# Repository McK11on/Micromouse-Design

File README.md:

# MicroMouse
Design and implementation of a micromouse robot for competitions, implementing filling algorithm and other technologies

| Layout | PCB_1 | PCB_2 |
|--------|-------|-------|
|  |  |  |

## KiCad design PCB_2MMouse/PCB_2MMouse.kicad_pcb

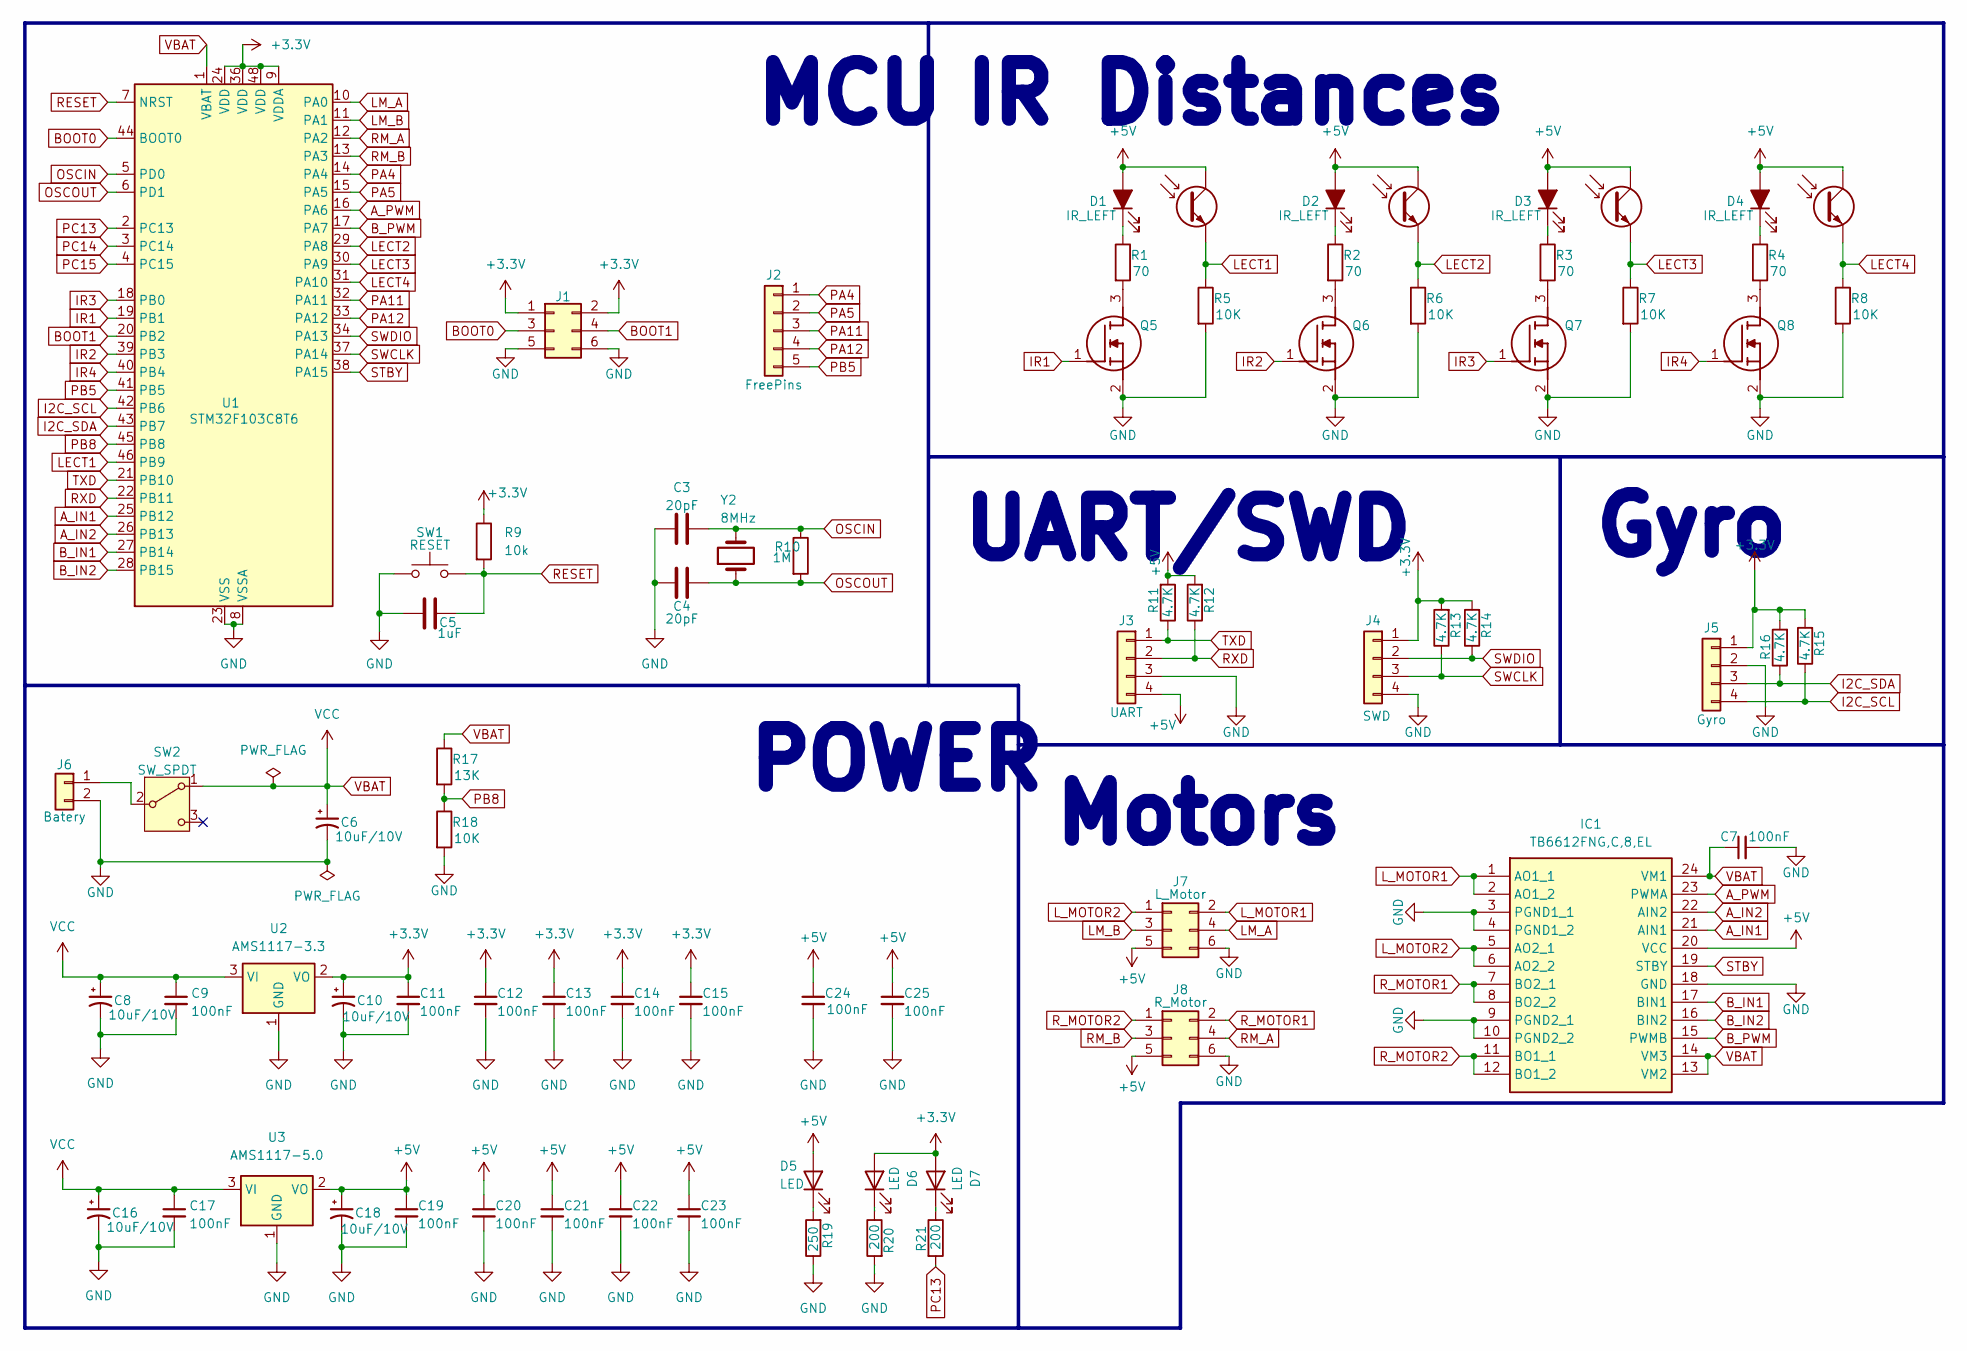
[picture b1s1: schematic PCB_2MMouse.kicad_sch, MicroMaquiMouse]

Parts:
C3, C4: 20pF; C_0805_2012Metric
C5: 1uF; C_0805_2012Metric_Pad1.18x1.45mm_HandSolder
C6, C8, C10, C16, C18: 10uF/10V; CP_EIA-3216-10_Kemet-I_Pad1.58x1.35mm_HandSolder
C7, C9, C11, C12, C13, C14, C15, C17, C19, C20, C21, C22, C23, C24, C25: 100nF; C_0805_2012Metric_Pad1.18x1.45mm_HandSolder
D1, D2, D3, D4: IR_LEFT; PinHeader_2x02_P2.00mm_Vertical
D5, D6, D7: LED; LED_1206_3216Metric
IC1: TB6612FNG,C,8,EL; SOP65P760X160-24N; Mouser Part Number 757-TB6612FNGC8EL
J1: Conn_02x03_Odd_Even; PinHeader_2x03_P2.00mm_Vertical
J2: FreePins; PinHeader_1x05_P2.00mm_Vertical
J3: UART; PinHeader_1x04_P2.00mm_Vertical
J4: SWD; PinHeader_1x04_P2.00mm_Vertical
J5: Gyro; PinSocket_1x04_P2.00mm_Vertical
J6: Batery; JST_EH_B2B-EH-A_1x02_P2.50mm_Vertical
J7: L_Motor; JST_EH_B6B-EH-A_1x06_P2.50mm_Vertical
J8: R_Motor; JST_EH_B6B-EH-A_1x06_P2.50mm_Vertical
Q5, Q6, Q7, Q8: IRLML6344TRPBF; SOT95P237X112-3N; Mouser Part Number 942-IRLML6344TRPBF
R1, R2, R3, R4: 70; R_0805_2012Metric_Pad1.20x1.40mm_HandSolder
R5, R6, R7, R8, R18: 10K; R_0805_2012Metric_Pad1.20x1.40mm_HandSolder
R9: 10k; R_0805_2012Metric_Pad1.20x1.40mm_HandSolder
R10: 1M; R_0805_2012Metric_Pad1.20x1.40mm_HandSolder
R11, R12, R13, R14, R15, R16: 4.7K; R_0805_2012Metric_Pad1.20x1.40mm_HandSolder
R17: 13K; R_0805_2012Metric_Pad1.20x1.40mm_HandSolder
R19: 250; R_0805_2012Metric_Pad1.20x1.40mm_HandSolder
R20, R21: 200; R_0805_2012Metric_Pad1.20x1.40mm_HandSolder
SW1: RESET; SW_Tactile_SPST_NO_Straight_CK_PTS636Sx25SMTRLFS
SW2: SW_SPDT; SW_CuK_JS202011CQN_DPDT_Straight
U1: STM32F103C8T6; LQFP-48_7x7mm_P0.5mm
U2: AMS1117-3.3; SOT-223-3_TabPin2
U3: AMS1117-5.0; SOT-223-3_TabPin2
Y2: 8MHz; Crystal_HC18-U_Vertical

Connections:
+3.3V: C10.1, C11.1, C12.1, C13.1, C14.1, C15.1, D6.2 (A), D7.2 (A), J1.1, J1.2, J4.1, J5.1, R9.1, R13.2, R14.2, R15.2, R16.2, U1.9 (VDDA), U1.24 (VDD), U1.36 (VDD), U1.48 (VDD), U2.2 (VO)
+5V: C18.1, C19.1, C20.1, C21.1, C22.1, C23.1, C24.1, C25.1, D1.2 (A), D1.4 (C), D2.2 (A), D2.4 (C), D3.2 (A), D3.4 (C), D4.2 (A), D4.4 (C), D5.2 (A), IC1.20 (VCC), J3.4, J7.5, J8.5, R11.2, R12.2, U3.2 (VO)
A_IN1: IC1.21 (AIN1), U1.25 (PB12)
A_IN2: IC1.22 (AIN2), U1.26 (PB13)
A_PWM: IC1.23 (PWMA), U1.16 (PA6)
BOOT0: J1.3, U1.44 (BOOT0)
BOOT1: J1.4, U1.20 (PB2)
B_IN1: IC1.17 (BIN1), U1.27 (PB14)
B_IN2: IC1.16 (BIN2), U1.28 (PB15)
B_PWM: IC1.15 (PWMB), U1.17 (PA7)
GND: C3.1, C4.1, C5.2, C6.2, C7.2, C8.2, C9.2, C10.2, C11.2, C12.2, C13.2, C14.2, C15.2, C16.2, C17.2, C18.2, C19.2, C20.2, C21.2, C22.2, C23.2, C24.2, C25.2, IC1.3 (PGND1_1), IC1.4 (PGND1_2), IC1.9 (PGND2_1), IC1.10 (PGND2_2), IC1.18 (GND), J1.5, J1.6, J3.3, J4.4, J5.2, J6.2, J7.6, J8.6, Q5.2 (S), Q6.2 (S), Q7.2 (S), Q8.2 (S), R5.2, R6.2, R7.2, R8.2, R18.2, R19.1, R20.2, SW1.1 (A), U1.8 (VSSA), U1.23 (VSS), U1.35 (VSS), U1.47 (VSS), U2.1 (GND), U3.1 (GND)
I2C_SCL: J5.4, R15.1, U1.42 (PB6)
I2C_SDA: J5.3, R16.1, U1.43 (PB7)
IR1: Q5.1 (G), U1.19 (PB1)
IR2: Q6.1 (G), U1.39 (PB3)
IR3: Q7.1 (G), U1.18 (PB0)
IR4: Q8.1 (G), U1.40 (PB4)
LECT1: D1.3 (E), R5.1, U1.46 (PB9)
LECT2: D2.3 (E), R6.1, U1.29 (PA8)
LECT3: D3.3 (E), R7.1, U1.30 (PA9)
LECT4: D4.3 (E), R8.1, U1.31 (PA10)
LM_A: J7.4, U1.10 (PA0)
LM_B: J7.3, U1.11 (PA1)
L_MOTOR1: IC1.1 (AO1_1), IC1.2 (AO1_2), J7.2
L_MOTOR2: IC1.5 (AO2_1), IC1.6 (AO2_2), J7.1
unnamed: D1.1 (K), R1.1
unnamed: D2.1 (K), R2.1
unnamed: D3.1 (K), R3.1
unnamed: D4.1 (K), R4.1
unnamed: D5.1 (K), R19.2
unnamed: D6.1 (K), R20.1
unnamed: D7.1 (K), R21.1
unnamed: J6.1, SW2.2 (B)
unnamed: Q5.3 (D), R1.2
unnamed: Q6.3 (D), R2.2
unnamed: Q7.3 (D), R3.2
unnamed: Q8.3 (D), R4.2
OSCIN: C3.2, R10.1, U1.5 (PD0), Y2.2
OSCOUT: C4.2, R10.2, U1.6 (PD1), Y2.1
PA4: J2.1, U1.14 (PA4)
PA5: J2.2, U1.15 (PA5)
PA11: J2.3, U1.32 (PA11)
PA12: J2.4, U1.33 (PA12)
PB5: J2.5, U1.41 (PB5)
PB8: R17.2, R18.1, U1.45 (PB8)
PC13: R21.2, U1.2 (PC13)
PC14: U1.3 (PC14)
PC15: U1.4 (PC15)
RESET: C5.1, R9.2, SW1.2 (B), U1.7 (NRST)
RM_A: J8.4, U1.12 (PA2)
RM_B: J8.3, U1.13 (PA3)
RXD: J3.2, R12.1, U1.22 (PB11)
R_MOTOR1: IC1.7 (BO2_1), IC1.8 (BO2_2), J8.2
R_MOTOR2: IC1.11 (BO1_1), IC1.12 (BO1_2), J8.1
STBY: IC1.19 (STBY), U1.38 (PA15)
SWCLK: J4.3, R13.1, U1.37 (PA14)
SWDIO: J4.2, R14.1, U1.34 (PA13)
TXD: J3.1, R11.1, U1.21 (PB10)
VBAT: C6.1, C7.1, C8.1, C9.1, C16.1, C17.1, IC1.13 (VM2), IC1.14 (VM3), IC1.24 (VM1), R17.1, SW2.1 (A), U1.1 (VBAT), U2.3 (VI), U3.3 (VI)

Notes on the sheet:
IR Distances
Motors
MCU
Gyro
POWER
UART/SWD

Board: 2 copper layers, 70 parts (22 on the bottom side), 57 nets, no tracks yet.

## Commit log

2023-09-20 Print Hello World
2023-09-20 Add new branch
2023-09-24 Add principal maze algorithm
2023-09-29 Add DFS(deep first search) method
2023-09-29 Add (breadth first search) method
2023-09-29 Add modifications in the principal maze creator
2023-09-29 Graphic modifications in searcher algorithms
2023-09-29 Add maze for testing
2023-09-29 Add Astart method
2023-10-10 Add some test changes/changing branch
2023-10-10 example
2023-10-10 First commit of the new branch for coppelia simulations
2023-10-10 Add api files for controlling through python
2024-02-23 Add PCB design (schematics and layout)
2024-02-23 Add visual support
2024-02-23 Create img
2024-02-23 Rename Layout.png to img/Layout.png
2024-02-23 Rename PCB_2.png to img/PCB_2.png
2024-02-23 Rename PCB_1.png to img/PCB_1.png
2024-02-23 Add Schematics
